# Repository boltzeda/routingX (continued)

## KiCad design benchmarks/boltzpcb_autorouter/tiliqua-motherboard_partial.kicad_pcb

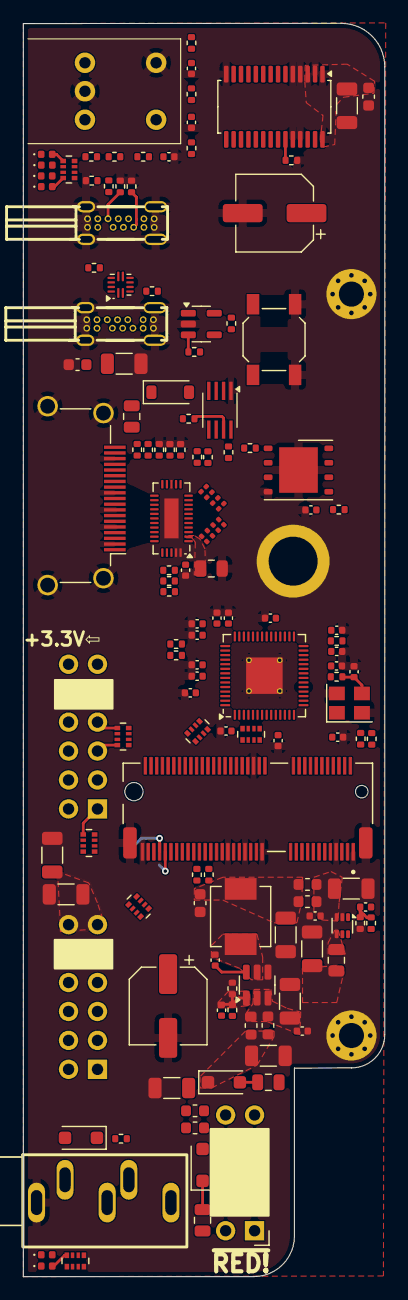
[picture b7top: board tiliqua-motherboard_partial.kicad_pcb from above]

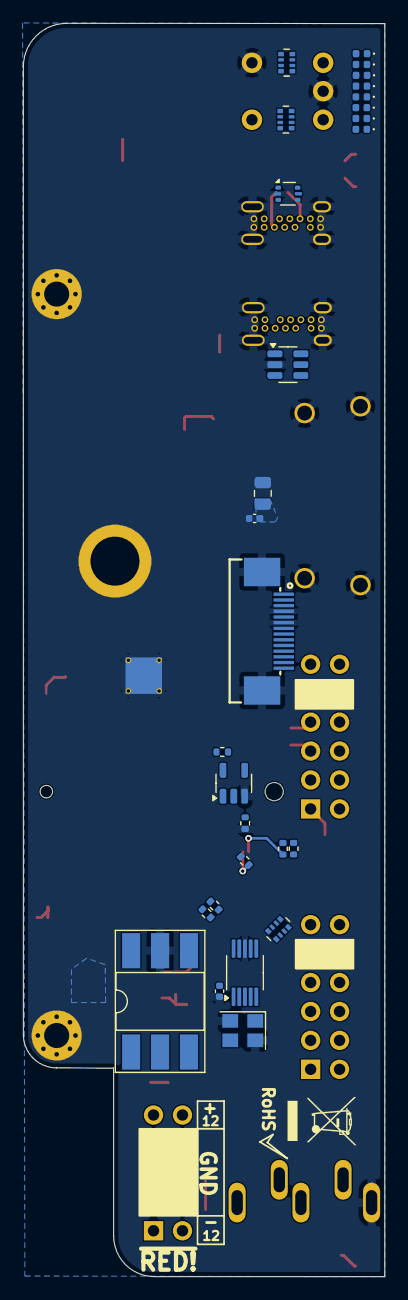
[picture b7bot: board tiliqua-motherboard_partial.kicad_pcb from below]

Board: 6 copper layers, 31.7 x 110.0 mm, 170 parts (28 on the bottom side), 195 nets.

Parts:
C1, C2, C3, C4, C5, C6, C7, C8, C9, C10, C13, C14, C36: 0.1uF; C_0402_1005Metric
C11, C12: 2.2uF; C_0402_1005Metric
C15, C16: 15pF; C_0402_1005Metric
C17: 6.8pF; C_0402_1005Metric
C19, C20, C22, C23, C24, C26, C29, C32, C38, C42: 22uF; C_1206_3216Metric
C21, C33: 100uF/10V; CP_Elec_6.3x5.4
C25, C28, C30, C35, C37: 100nF; C_0402_1005Metric
C27, C34, C43: 100nF; C_0603_1608Metric
C31: 100pF; C_0402_1005Metric
C39, C40, C41: 10n; C_0402_1005Metric
C44, C45: 4.7uF; C_0805_2012Metric
C46, C47, C48, C49, C50, C51, C52, C53: 100nF; C_0201_0603Metric
D1, D2, D3: 1N4007FL; D_SOD-123F
D4: B0520LW; D_SOD-123
D5, D6, D7, D8, D13, D14, D16: LED 0402 GREEN; LED_0402_1005Metric
D9, D10, D11, D12, D17, D18, D20: LED 0402 RED; LED_0402_1005Metric
F1: 16V 500mA; Fuse_0805_2012Metric
F2: 15V 200mA; Fuse_0805_2012Metric
F3: 15V 50mA; Fuse_0805_2012Metric
H1, H2: MountingHole; MountingHole_2.2mm_M2_Pad_Via
H3: MountingHole; mounting_hole
J1: Conn_01x15; FFC_0.5-14P_CTXJ-H2.0_1
J2, J3: Conn_02x06_Top_Bottom; PinSocket_2x06_P2.54mm_Horizontal
J4: AUDIO-TH_PJ-325M
J5, J7: USB_C_Receptacle_USB2.0_14P; USB-C-TH_U264-141N-4BAC10
J6: CONN 2x5 P=2.54mm; PinHeader_2x05_P2.54mm_Horizontal
J8: MICROMOD-2222; TE_21992304
J10: DVI_GPDI; HDMI_A_Amphenol_10029449-x01xLF_Horizontal
L1, L2, L4, L5, L6, L7: FERRITE; L_0603_1608Metric
L3: 10uH 2A; L_Vishay_IHLP-2020
L8: 2.2uH; L_0805_2012Metric
R1, R2, R9, R19, R25, R26, R32, R44, R50: 4K7; R_0402_1005Metric
R3, R4, R13, R14, R21, R22, R23, R27, R29, R30, R33, R45: 10K; R_0402_1005Metric
R5, R15: 1K; R_0402_1005Metric
R6, R7: 27R; R_0402_1005Metric
R8: 100R; R_0402_1005Metric
R10, R16: 220R; R_0402_1005Metric
R11, R12: 5.1K; R_0402_1005Metric
R17: 157K (158K); R_0402_1005Metric
R18: 30K; R_0402_1005Metric
R20: 900K (910K); R_0402_1005Metric
R24: 18K; R_0402_1005Metric
R28, R31: 2K2; R_0402_1005Metric
R34, R35, R40, R41, R47, R48, R49: 33R; R_0402_1005Metric
R36, R37, R42: 47K; R_0402_1005Metric
R38: 200K; R_0402_1005Metric
R39: 210K; R_0402_1005Metric
R46: 0R; R_0402_1005Metric
RN1, RN2, RN3, RN4: 220R; R_Array_Convex_4x0402
RN5, RN6, RN7, RN8, RN9, RN10: 33R; R_Array_Convex_4x0402
SW2: SW_Tactile_SPST; SW_SPST_SKQG_WithStem
SW3: RotaryEncoder_Switch; RotaryEncoder_Bourns_Horizontal_PEC09-2xxxF-Sxxxx
U1: USBLC6-2P6; SOT-666
U2: RP2040(QFN-56_7x7mm_P0.4mm); QFN-56-1EP_7x7mm_P0.4mm_EP3.2x3.2mm_ThermalVias
U3: USBLC6-4SC6; SOT-23-6
U4: H11L1SR2M; DIP-6_W8.89mm_SMDSocket_LongPads
U5: AP63200WU; TSOT-23-6
U6: 74AUC1G79; SOT-23-5
U7: PCA9635 LED DRIVER; TSSOP-28_4.4x9.7mm_P0.65mm
U8: TUSB322I; Texas_X2QFN-12_1.6x1.6mm_P0.4mm
U9: AP2161W; SOT-23-5
U10: TLV62569ADRLR; SOT-563
U11: Si5351A-B-GT; MSOP-10_3x3mm_P0.5mm
U12: W25Q128JVP; WSON-8-1EP_6x5mm_P1.27mm_EP3.4x4mm
U13: PI3HDX511E; Diodes_ZL32_TQFN-32-1EP_3x6mm_P0.4mm_EP1.25x3.5mm
U14: PCA9306; SSOP-8_2.95x2.8mm_P0.65mm
Y1: Crystal_GND24_Small; Crystal_SMD_3225-4Pin_3.2x2.5mm
Y2: 25MHz AMB8G; Crystal_SMD_3225-4Pin_3.2x2.5mm

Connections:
+3V3: C1.2, C3.1, C4.1, C5.1, C6.1, C7.1, C8.1, C9.1, C10.1, C11.1, C17.1, C21.1, C22.1, C24.1, C32.1, C33.1, C35.1, C36.1, C37.1, C42.1, C43.1, C44.1, J1.5, J2.6, J2.12, J3.6, J3.12, J8.2 (3.3V), J8.74 (3.3V), L8.2, R1.2, R2.2, R3.1, R4.1, R13.1, R14.1, R15.2, R19.2, R21.1, R27.1, R33.1, R36.2, R37.2, R38.2, R39.2, R44.1, R50.1, RN1.1 (R1.1), RN1.2 (R2.1), RN1.3 (R3.1), RN1.4 (R4.1), RN2.1 (R1.1), RN2.2 (R2.1), RN2.3 (R3.1), RN2.4 (R4.1), RN3.1 (R1.1), RN3.2 (R2.1), RN3.3 (R3.1), RN3.4 (R4.1), RN4.1 (R1.1), RN4.2 (R2.1), RN4.3 (R3.1), RN4.4 (R4.1), U2.1 (IOVDD), U2.10 (IOVDD), U2.22 (IOVDD), U2.33 (IOVDD), U2.42 (IOVDD), U2.43 (ADC_AVDD), U2.44 (VREG_VIN), U2.48 (USB_VDD), U2.49 (IOVDD), U4.6, U6.5 (VCC), U7.1 (A0), U7.3 (A2), U7.28 (VDD), U11.1 (VDD), U11.7 (VDDO), U12.8 (VCC), U13.1 (VDD), U13.22 (VDD), U14.2 (VREF1)
+5V: C31.2, C34.1, C38.1, D4.2 (A), L3.2, L4.2, L5.2, R17.2, U8.12 (VDD), U9.5 (IN)
+12V: C23.1, C25.1, J1.3, L1.1, L6.2, U5.2 (EN), U5.3 (IN)
-12V: J1.1, L2.1, L7.2
/gpdi/CONN_CK+: J10.10 (CK+), U13.19 (OUT_CLK-)
/gpdi/CONN_CK-: J10.12 (CK-), U13.18 (OUT_CLK+)
/gpdi/CONN_D0+: J10.7 (D0+), U13.21 (OUT_D2-)
/gpdi/CONN_D0-: J10.9 (D0-), U13.20 (OUT_D2+)
/gpdi/CONN_D1+: J10.4 (D1+), U13.24 (OUT_D1-)
/gpdi/CONN_D1-: J10.6 (D1-), U13.23 (OUT_D1+)
/gpdi/CONN_D2+: J10.1 (D2+), U13.26 (OUT_D0-)
/gpdi/CONN_D2-: J10.3 (D2-), U13.25 (OUT_D0+)
/gpdi/HPD_Sink: J10.19 (HPD), U13.29 (HPD_Sink)
/gpdi/SCL_Sink: J10.15 (SCL), R28.1, U13.27 (SCL_Sink)
/gpdi/SDA_Sink: J10.16 (SDA), R31.1, U13.28 (SDA_Sink)
/led_driver/~OE: R32.2, U7.23 (~OE)
/pmod_audio/PDN: J1.12, R46.1, U6.4 (Q)
/rp2040_jtag/I2C0_SCL: R40.1, U2.41 (GPIO29/ADC3/SPI1_CSn/UART0_RX/I2C0_SCL/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)
/rp2040_jtag/I2C0_SDA: R41.1, U2.40 (GPIO28/ADC2/SPI1_RX/UART0_TX/I2C0_SDA/P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)
/rp2040_jtag/RP2040_USB_D+: J5.A6 (D+), J5.B6 (D+), R7.1, U1.3 (I/O2), U1.4 (I/O2)
/rp2040_jtag/RP2040_USB_D-: J5.A7 (D-), J5.B7 (D-), R6.1, U1.1 (I/O1), U1.6 (I/O1)
/rp2040_jtag/RP2040_USB_VBUS: J5.A4 (VBUS), J5.A9 (VBUS), J5.B4 (VBUS), J5.B9 (VBUS), R23.2, U1.5 (VBUS)
/rp2040_jtag/SPI0_CSn: RN8.8 (R1.2), U2.3 (GPIO1/SPI0_CSn/UART0_RX/I2C0_SCL/PWM0_B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)
/rp2040_jtag/SPI0_RX: RN8.5 (R4.2), U2.6 (GPIO4/SPI0_RX/UART1_TX/I2C0_SDA/PWM2_A/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)
/rp2040_jtag/SPI0_SCK: RN8.7 (R2.2), U2.4 (GPIO2/SPI0_SCK/UART0_CTS/I2C1_SDA/PWM1_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)
/rp2040_jtag/SPI0_TX: RN8.6 (R3.2), U2.5 (GPIO3/SPI0_TX/UART0_RTS/I2C1_SCL/PWM1_B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)
/usbc/USB_CC1: J7.A5 (CC1), U3.4 (I/O3), U8.1 (CC1)
/usbc/USB_CC2: J7.B5 (CC2), U3.3 (I/O2), U8.2 (CC2)
/usbc/~USB_VBUS_FLG: R27.2, U9.3 (~FLG)
ECP5_M10_TDO: J8.23 (SWDIO), U2.28 (GPIO17/SPI0_CSn/UART0_RX/I2C0_SCL/PWM0_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)
ECP5_R11_TDI: J8.18 (D1/CAM_TRIG), U2.27 (GPIO16/SPI0_RX/UART0_TX/I2C0_SDA/PWM0_A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)
ECP5_T10_TCK: J8.10 (D0), U2.29 (GPIO18/SPI0_SCK/UART0_CTS/I2C1_SDA/PWM1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)
ECP5_T11_TMS: J8.21 (SWDCK), U2.30 (GPIO19/SPI0_TX/UART0_RTS/I2C1_SCL/PWM1_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)
ENC_A: C41.1, J8.8 (G11), R29.2
ENC_B: C40.1, J8.12 (I2C_SDA), R30.2
ENC_S: C39.1, J8.43 (CAN-TX), R22.2
EX1_1: J8.55 (SPI_~CS), RN9.2 (R2.1)
EX1_2: J8.38 (A1), RN8.1 (R1.1), RN9.4 (R4.1)
EX1_3: J8.66 (SDIO_DATA1), RN10.5 (R4.2)
EX1_4: J8.41 (CAN-RX), RN10.8 (R1.2)
EX1_7: J8.57 (SPI_SCK), RN9.1 (R1.1)
EX1_8: J8.35 (USBHOST_D+), RN9.3 (R3.1)
EX1_9: J8.34 (A0), RN8.2 (R2.1), RN10.6 (R3.2)
EX1_10: J8.73 (G5/BUS5), RN10.7 (R2.2)
EX2_1: J8.59 (SPI_SDO), RN6.1 (R1.1)
EX2_2: J8.63 (G10/ADC_D+/CAM_VSYNC), RN6.3 (R3.1)
EX2_3: J8.14 (I2C_SCL), RN7.8 (R1.2)
EX2_4: J8.20 (RX2), RN7.7 (R2.2), RN8.3 (R3.1)
EX2_7: J8.61 (SPI_SDI), RN6.2 (R2.1)
EX2_8: J8.15 (CTS1), RN7.5 (R4.2)
EX2_9: J8.13 (RTS1), RN6.4 (R4.1)
EX2_10: J8.22 (TX2), RN7.6 (R3.2), RN8.4 (R4.1)
FFC_BICK: J1.10, RN5.4 (R4.1)
FFC_LRCK: J1.9, RN5.3 (R3.1)
FFC_MCLK: J1.11, R49.2
FFC_PDN_CLK: J8.56 (AUD_OUT/CAM_MCLK), R45.2, U6.2 (C)
FFC_PDN_D: J8.65 (G9/ADC_D-/CAM_HSYNC), R46.2, U6.1 (D)
FFC_SCL: J1.14, R34.2
FFC_SDA: J1.13, R35.2
FFC_SDIN1: J1.7, RN5.1 (R1.1)
FFC_SDOUT1: J1.8, RN5.2 (R2.1)
GND: C1.1, C2.2, C3.2, C4.2, C5.2, C6.2, C7.2, C8.2, C9.2, C10.2, C11.2, C12.2, C13.2, C14.2, C15.2, C16.2, C19.2, C20.1, C21.2, C22.2, C23.2, C24.2, C25.2, C26.2, C27.2, C28.2, C29.2, C32.2, C33.2, C34.2, C35.2, C36.2, C37.2, C38.2, C39.2, C40.2, C41.2, C42.2, C43.2, C44.2, C45.1, H1.1, H2.1, H3.1, J1.4, J1.6, J1.15, J2.5, J2.11, J3.5, J3.11, J4.G, J5.A1 (GND), J5.A12 (GND), J5.B1 (GND), J5.B12 (GND), J5.S1 (SHIELD), J6.3, J6.4, J6.5, J6.6, J6.7, J6.8, J7.A1 (GND), J7.A12 (GND), J7.B1 (GND), J7.B12 (GND), J7.S1 (SHIELD), J8.1 (GND), J8.7 (GND), J8.33 (GND), J8.36 (GND), J8.39 (GND), J8.45 (GND), J8.75 (GND), J8.S1 (GND), J8.S2 (GND), J10.2 (D2S), J10.5 (D1S), J10.8 (D0S), J10.11 (CKS), J10.17 (GND), J10.SH, R9.1, R11.2, R12.2, R18.1, R24.1, R25.1, R26.1, R32.1, R42.1, R45.1, SW2.1, SW3.C, SW3.S1, U1.2 (GND), U2.19 (TESTEN(GND)), U2.57 (GND(EPAD)), U3.2 (GND), U4.5, U5.4 (GND), U6.3 (GND), U7.2 (A1), U7.4 (A3), U7.5 (A4), U7.14 (VSS), U7.24 (A5), U7.25 (A6), U8.5 (ADDR), U8.10 (GND), U8.11 (~EN), U9.2 (GND), U10.2 (GND), U11.8 (GND), U12.4 (GND), U12.9 (GND), U13.14 (GND), U13.31 (GND), U13.32 (GND), U13.33 (HGND), U14.1 (GND), Y1.2, Y1.4, Y2.2, Y2.4
GPDI_CK+: C52.1, J8.62 (SPI_SDO1/SDIO_CMD)
GPDI_CK-: C53.1, J8.64 (SPI_SDI1/SDIO_DATA0)
GPDI_D0+: C50.1, J8.68 (SDIO_DATA2)
GPDI_D0-: C51.1, J8.70 (SPI_~CS1/SDIO_DATA3)
GPDI_D1+: C48.1, J8.52 (AUD_LRCLK)
GPDI_D1-: C49.1, J8.54 (AUD_IN/CAM_PCLK)
GPDI_D2+: C46.1, J8.60 (SPI_SCK1/SDIO_CLK)
GPDI_D2-: C47.1, J8.58 (AUD_MCLK)
GPDI_DDC_EN: J8.11 (~BOOT), U14.8 (EN)
GPDI_HPD: J8.37 (USBHOST_D-), R44.2, U13.11 (HPD_SRC)
MIDI_RX: J8.6 (~RESET), R16.1
MOBO_I2C_SCL: J8.53 (I2C_SCL1), R1.1, R40.2, U7.26 (SCL), U8.8 (SCL/OUT2), U11.4 (SCL), U14.3 (SCL1)
MOBO_I2C_SDA: J8.51 (I2C_SDA1), R2.1, R41.2, U7.27 (SDA), U8.7 (SDA/OUT1), U11.5 (SDA), U14.4 (SDA1)
unnamed: C15.1, R5.1, Y1.3
unnamed: D1.2 (A), J4.T, U4.2
unnamed: D1.1 (K), R10.2, U4.1
unnamed: D2.2 (A), F1.2
unnamed: C20.2, D2.1 (K), L1.2, L6.1
unnamed: C19.1, D3.2 (A), L2.2, L7.1
unnamed: D3.1 (K), F2.2
unnamed: D4.1 (K), F3.2, R28.2, R31.2
unnamed: D5.2 (A), RN1.8 (R1.2)
unnamed: D5.1 (K), U7.6 (LED0)
unnamed: D6.2 (A), RN2.8 (R1.2)
unnamed: D6.1 (K), U7.10 (LED4)
unnamed: D7.2 (A), RN3.8 (R1.2)
unnamed: D7.1 (K), U7.15 (LED8)
unnamed: D8.2 (A), RN4.8 (R1.2)
unnamed: D8.1 (K), U7.19 (LED12)
unnamed: D9.2 (A), RN1.7 (R2.2)
unnamed: D9.1 (K), U7.7 (LED1)
unnamed: D10.2 (A), RN2.7 (R2.2)
unnamed: D10.1 (K), U7.11 (LED5)
unnamed: D11.2 (A), RN3.7 (R2.2)
unnamed: D11.1 (K), U7.16 (LED9)
unnamed: D12.2 (A), RN4.7 (R2.2)
unnamed: D12.1 (K), U7.20 (LED13)
unnamed: D13.2 (A), RN1.6 (R3.2)
unnamed: D13.1 (K), U7.8 (LED2)
unnamed: D14.2 (A), RN2.6 (R3.2)
unnamed: D14.1 (K), U7.12 (LED6)
unnamed: D16.2 (A), RN4.6 (R3.2)
unnamed: D16.1 (K), U7.21 (LED14)
unnamed: D17.2 (A), RN1.5 (R4.2)
unnamed: D17.1 (K), U7.9 (LED3)
unnamed: D18.2 (A), RN2.5 (R4.2)
unnamed: D18.1 (K), U7.13 (LED7)
unnamed: D20.2 (A), RN4.5 (R4.2)
unnamed: D20.1 (K), U7.22 (LED15)
unnamed: J2.1, RN6.8 (R1.2)
unnamed: J2.2, RN6.6 (R3.2)
unnamed: J2.3, RN7.1 (R1.1)
unnamed: J2.4, RN7.2 (R2.1)
unnamed: J2.7, RN6.7 (R2.2)
unnamed: J2.8, RN7.4 (R4.1)
unnamed: J2.9, RN6.5 (R4.2)
unnamed: J2.10, RN7.3 (R3.1)
unnamed: J3.1, RN9.5 (R4.2)
unnamed: J3.2, RN9.6 (R3.2)
unnamed: J3.3, RN10.4 (R4.1)
unnamed: J3.4, RN10.1 (R1.1)
unnamed: J3.7, RN9.8 (R1.2)
unnamed: J3.8, RN9.7 (R2.2)
unnamed: J3.9, RN10.3 (R3.1)
unnamed: J3.10, RN10.2 (R2.1)
unnamed: J4.S, R10.1
unnamed: J5.A5 (CC1), R11.1
unnamed: J5.B5 (CC2), R12.1
unnamed: F2.1, J6.1, J6.2
unnamed: F1.1, J6.9, J6.10
unnamed: J8.50 (AUD_BCLK), RN5.5 (R4.2)
unnamed: J8.42 (G1/BUS1), RN5.8 (R1.2)
unnamed: J8.46 (G3/BUS3), RN5.7 (R2.2)
unnamed: J8.48 (G4/BUS4), RN5.6 (R3.2)
unnamed: J8.71 (G6/BUS6), R35.1
unnamed: J8.69 (G7/BUS7), R34.1
unnamed: J8.67 (G8), R49.1
unnamed: F3.1, J10.18 (+5V)
unnamed: R8.2, SW2.2
unnamed: R13.2, R22.1, SW3.S2
unnamed: R14.2, R29.1, SW3.B
unnamed: R15.1, R16.2, U4.4
unnamed: R21.2, R30.1, SW3.A
unnamed: R23.1, R24.2, U2.34 (GPIO22/SPI0_SCK/UART1_CTS/I2C1_SDA/PWM3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)
unnamed: C2.1, R4.2, U2.26 (RUN(RESET#))
unnamed: R6.2, U2.46 (USB_DM)
unnamed: R7.2, U2.47 (USB_DP)
unnamed: C12.1, C13.1, C14.1, U2.23 (DVDD), U2.45 (VREG_VOUT), U2.50 (DVDD)
unnamed: C16.1, U2.20 (XIN), Y1.1
unnamed: R5.2, U2.21 (XOUT)
unnamed: C30.1, U5.6 (BST)
unnamed: C31.1, R17.1, R18.2, U5.1 (FB)
unnamed: C30.2, L3.1, U5.5 (SW)
unnamed: R20.2, U8.3 (VBUS_DET)
unnamed: C28.1, C29.1, L4.1, L5.1, U10.3 (VIN), U10.5 (EN)
unnamed: C17.2, R39.1, R42.2, U10.1 (FB)
unnamed: L8.1, U10.4 (SW)
unnamed: R47.1, U11.10 (CLK0)
unnamed: R48.1, U11.9 (CLK1)
unnamed: U11.2 (XA), Y2.3
unnamed: U11.3 (XB), Y2.1
unnamed: U2.52 (QSPI_SCLK(Soft_GPIO)), U12.6 (CLK)
unnamed: U2.53 (QSPI_SD0(Soft_GPIO)), U12.5 (DI(IO0))
unnamed: U2.55 (QSPI_SD1(Soft_GPIO)), U12.2 (DO(IO1))
unnamed: U2.54 (QSPI_SD2(Soft_GPIO)), U12.3 (IO2)
unnamed: U2.51 (QSPI_SD3(Soft_GPIO)), U12.7 (IO3)
unnamed: R3.2, R8.1, U2.56 (QSPI_SS_N(Soft_GPIO)), U12.1 (~CS)
unnamed: C45.2, U13.2 (CEXT)
unnamed: R26.2, U13.17 (EQ_S0)
unnamed: C53.2, U13.10 (IN_CLK+)
unnamed: C52.2, U13.9 (IN_CLK-)
unnamed: C51.2, U13.8 (IN_D0+)
unnamed: C50.2, U13.7 (IN_D0-)
unnamed: C49.2, U13.6 (IN_D1+)
unnamed: C48.2, U13.5 (IN_D1-)
unnamed: C47.2, U13.4 (IN_D2+)
unnamed: C46.2, U13.3 (IN_D2-)
unnamed: R25.2, U13.16 (OC_S0)
unnamed: R9.2, U13.15 (ROUT_S0)
unnamed: R37.1, U13.13 (SCL_SRC), U14.6 (SCL2)
unnamed: R36.1, U13.12 (SDA_SRC), U14.5 (SDA2)
unnamed: R50.2, U13.30 (~OE)
unnamed: R38.1, U14.7 (VREF2)
PLL_CLK0: J8.44 (G2/BUS2), R47.2
PLL_CLK1: J8.40 (G0/BUS0), R48.2
RP2040_UART0_RX: J8.17 (TX1), U2.16 (GPIO13/SPI1_CSn/UART0_RX/I2C0_SCL/PWM6_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)
RP2040_UART0_TX: J8.19 (RX1), U2.15 (GPIO12/SPI1_RX/UART0_TX/I2C0_SDA/PWM6_A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)
SC_USB0_D+: J7.A6 (D+), J7.B6 (D+), J8.3 (USB_D+), U3.1 (I/O1)
SC_USB0_D-: J7.A7 (D-), J7.B7 (D-), J8.5 (USB_D-), U3.6 (I/O4)
SC_USB0_ID: J8.16 (I2C_~INT), R19.1, U8.9 (ID)
SC_USB0_VBUS: C26.1, C27.1, J7.A4 (VBUS), J7.A9 (VBUS), J7.B4 (VBUS), J7.B9 (VBUS), J8.9 (USB_VIN), R20.1, U3.5 (VBUS), U9.1 (OUT)
USB_INT: J8.47 (PWM1), U8.6 (~INT/OUT3)
USB_VBUS_EN: J8.32 (PWM0), R33.2, U9.4 (~EN)
